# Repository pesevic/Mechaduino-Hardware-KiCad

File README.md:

# Overview
This repository contains an updated KiCad port of [jcchurch13's](https://github.com/jcchurch13/Mechaduino-Hardware) Mechaduino hardware. 

As a part of my master's thesis, I wanted to revive the Mechaduino-based [TorqueTuner](https://github.com/IDMIL/TorqueTuner), a rotary haptic device developed at the Input Devices and Music Interaction Laboratory (IDMIL) at McGill University. Since the Mechaduino has been out of production for some years, and because the original design files are in EAGLE (a now-defunct, proprietary software), I have ported the schematics and board layout to KiCad, a free and open-source (and incredibly powerful) PCB design software. 

While retaining the original circuit design, I have updated the schematics and created a new PCB layout from scratch, using KiCad's built-in component libraries. I have also included PCB fabrication/assembly files (.gbr, .drl, BOM, CPL). Most importantly, since the design is now more readily accessible, I hope it will be much easier to adapt and redesign the hardware for various stepper motors and applications.

Below, I have included some useful information if you wish to adopt or adapt the Mechaduino for your own project.

# Guide
This section serves as a guide for manufacturing and programming the Mechaduino.
## Mechaduino Summary
The [Mechaduino](https://github.com/jcchurch13/Mechaduino-Hardware) is an open-source stepper motor servo designed by [Tropical Labs](https://tropical-labs.com/mechaduino/). Its relatively small size and affordability make it attractive for mechatronics applications.

Integrated circuits on the board include a motor driver (A4954), magnetic encoder (AS5047D), 3.3 V linear voltage regulator (TLV70233), and an Arduino Zero-compatible microcontroller (ATSAMD21G18A-A). It can be powered via USB or an external 5 V source. The motor is powered through a terminal block, accepting a supply voltage between 8 V and 35 V. A range of Arduino I/O pins are accessible through the header pins, including those for I2C and SPI communication. See the schematic for more detail.

The board is designed to fit onto the back of a NEMA 17 motor.

## PCB Manufacturing
If you wish to obtain Mechaduino PCBs for yourself, you may follow what I suggest below, which is how I ordered them for myself.

For manufacturing and assembly, I used [jlcpcb.com](jlcpcb.com). Upload the zipped fabrication files to JLC, and add the PCB assembly option. Since two-layer boards can only be assembled on one side, choose the top side. The magnetic encoder and its decoupling capacitor can be soldered manually later. Upload the corresponding bill of materials and component position list .csv files. **Note that you may need to select alternative parts or reposition components in the board preview.** I have had to flip C12 and align J9 (USB connector) each time I've processed the PCBs.

## Device Assembly
Besides the Mechaduino PCB, you will need the following parts (the links direct to the parts I used):
 - [a NEMA 17 stepper motor](https://www.omc-stepperonline.com/nema-17-bipolar-45ncm-64oz-in-2a-42x42x40mm-4-wires-w-1m-cable-connector-17hs16-2004s1),
 - [a diametrically magnetized NdFeB magnet](https://www.digikey.ca/en/products/detail/radial-magnets-inc/8996/5126078),
 - an AS5074D magnetic encoder IC,
 - an 0.1 uF 0805 SMD capacitor,
 - 2.54 mm pitch header pins,
 - long M3 screws/threaded rods,
 - standoffs of some sort (I used washers), and
 - super glue.

Follow these steps (based on instructions in [Tropical Labs' manual](https://tropical-labs.com/wp-content/uploads/2018/11/Mechaduino-Manual-0.1.3.pdf)):
1. Solder the encoder and capacitor to the back of the PCB with an iron/reflow/oven. Also add the header pins.
2. Super glue the magnet onto the back of the motor shaft. Center it as much as possible.
3. Mount the PCB to the motor using the threaded rods and standoffs. The PCB should sit a couple of milimeters away from the motor.

Your Mechaduino should now be ready to be programmed.

## Programming
Flashing an Arduino Zero bootloader onto the custom MCU circuit was, for me, the most challenging part of this build. I used an ST-LINK V2 USB programmer paired with [Adafruit Adalink](https://github.com/adafruit/Adafruit_Adalink) to upload the bootloader via the PCB's SWD pins. This may be easier on Mac, but I can only speak for the Herculean procedure required for Windows users. Besides the USB programmer, you will need some way of connecting the programmer to the pins. I used an SWD breakout board connected to the programmer with jumper wires.

Follow the installation instructions on the [Adalink repository](https://github.com/adafruit/Adafruit_Adalink). Note, however, that I could not get Adalink to work with any version of Python newer than 2.7.13 (this was using Adalink 2.2.0 and OpenOCD 0.12.0). You may need to downgrade Python to an older version.

Once you have confirmed that Adalink is working in CMD, clone the [ArduinoCore-samd repository](https://github.com/arduino/arduinocore-samd) to get the bootloader. CD into `/ArduinoCore-samd/bootloaders/zero`. Wipe the board and flash the bootloader with the following two commands:
```
adalink atsamd21g18 -p stlink -w
adalink -v atsamd21g18 -p stlink -h samd21_sam_ba.hex
```
Check whether the 5888 bytes are verified. If not, unplugging and plugging the ST-LINK USB dongle into my computer seemed to fix things. Once the MCU has successfully been flashed, connect the Mechaduino to your computer via the micro-USB port. Double-pressing the reset button on the PCB should make the device appear as an Arduino Zero in Device Manager or in the Arduino IDE.

Finally, clone the [Mechaduino Firmware](https://github.com/jcchurch13/Mechaduino-Firmware) repository and upload the code to the board via the Arduino IDE. You should now have a fully functioning Mechaduino. Run the calibration routine and tests as described in [Tropical Labs' manual](https://tropical-labs.com/wp-content/uploads/2018/11/Mechaduino-Manual-0.1.3.pdf).

# License
This project is released under the [Creative Commons Attribution-ShareAlike 4.0](https://creativecommons.org/licenses/by-sa/4.0/) license, and is not endorsed by the original creator.

*No generative AI was used in any part of this project.*

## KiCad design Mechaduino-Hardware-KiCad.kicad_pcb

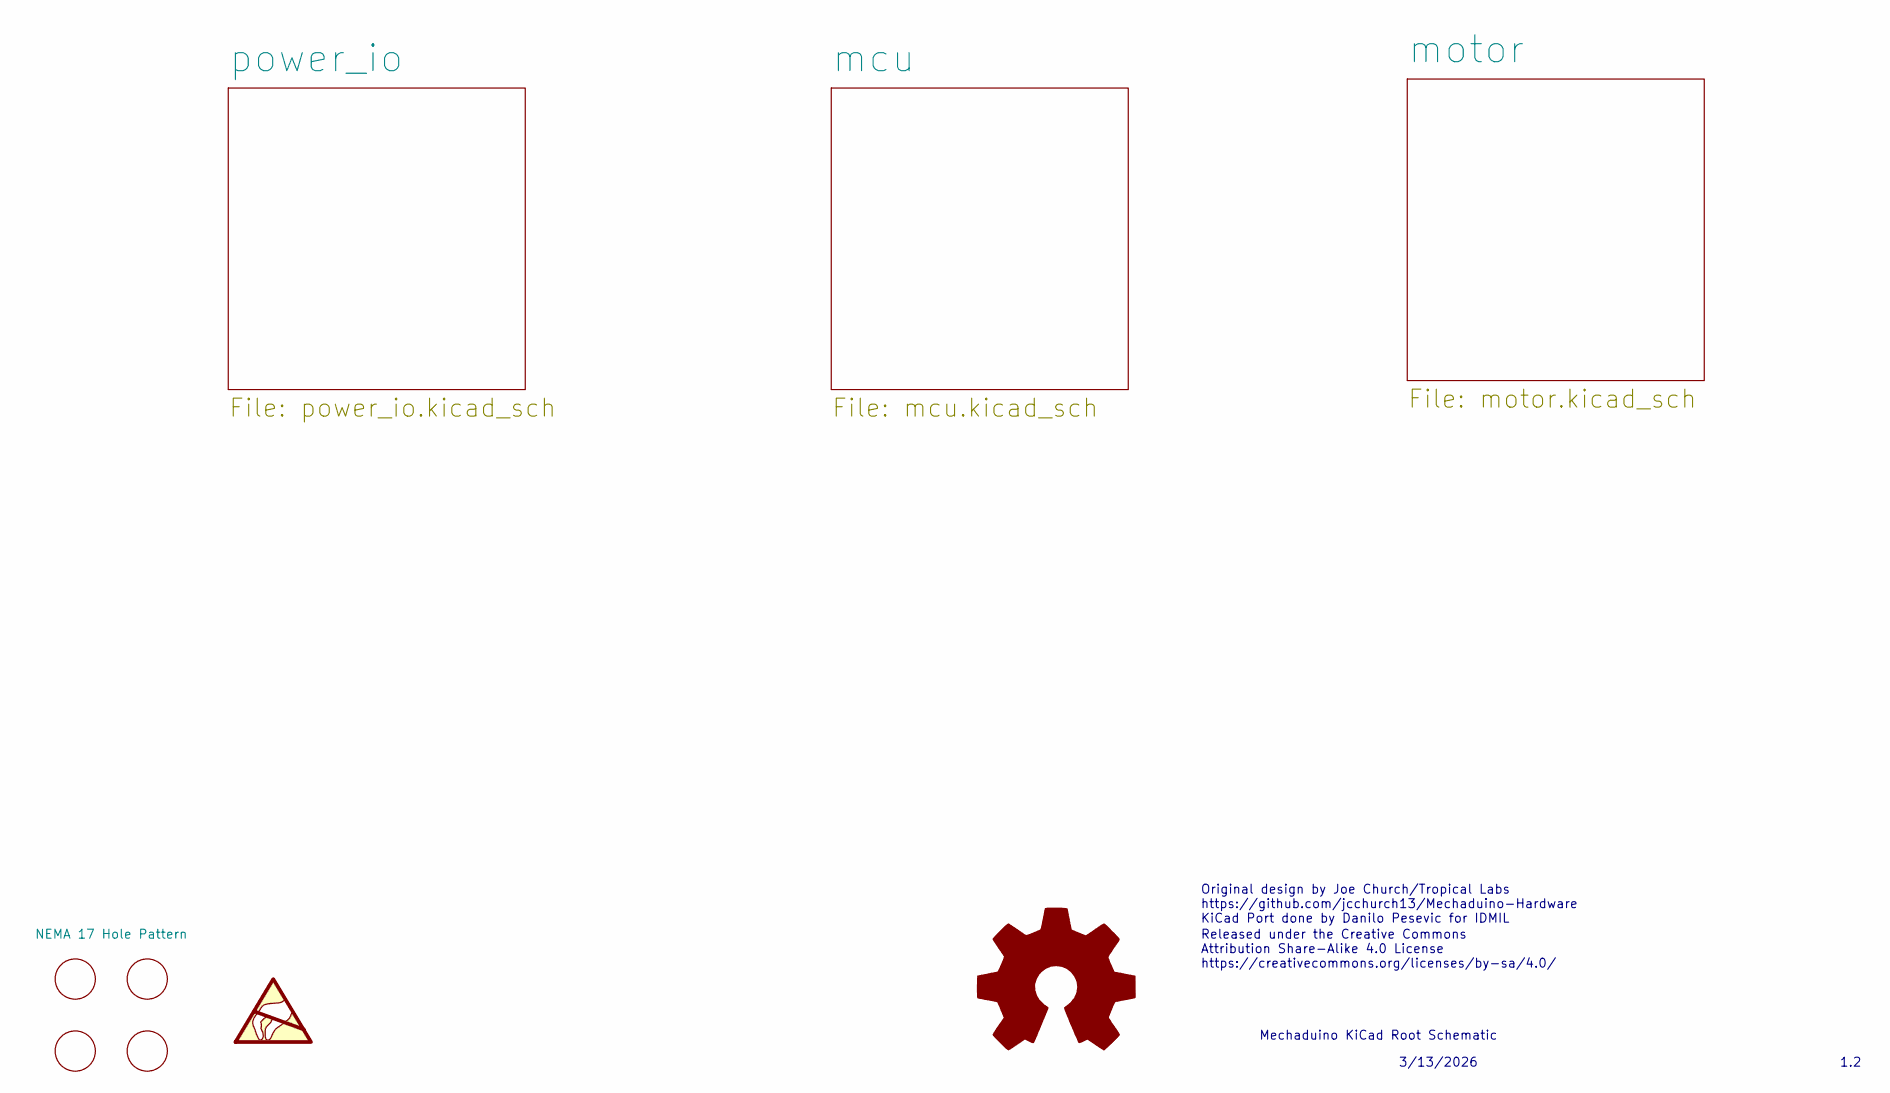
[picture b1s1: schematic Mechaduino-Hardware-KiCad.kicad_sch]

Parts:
J13: NEMA 17 Hole Pattern

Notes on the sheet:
Mechaduino KiCad Root Schematic
Original design by Joe Church/Tropical Labs https://github.com/jcchurch13/Mechaduino-Hardware KiCad Port done by Danilo Pesevic for IDMIL
3/13/2026
Released under the Creative Commons Attribution Share-Alike 4.0 License https://creativecommons.org/licenses/by-sa/4.0/
1.2

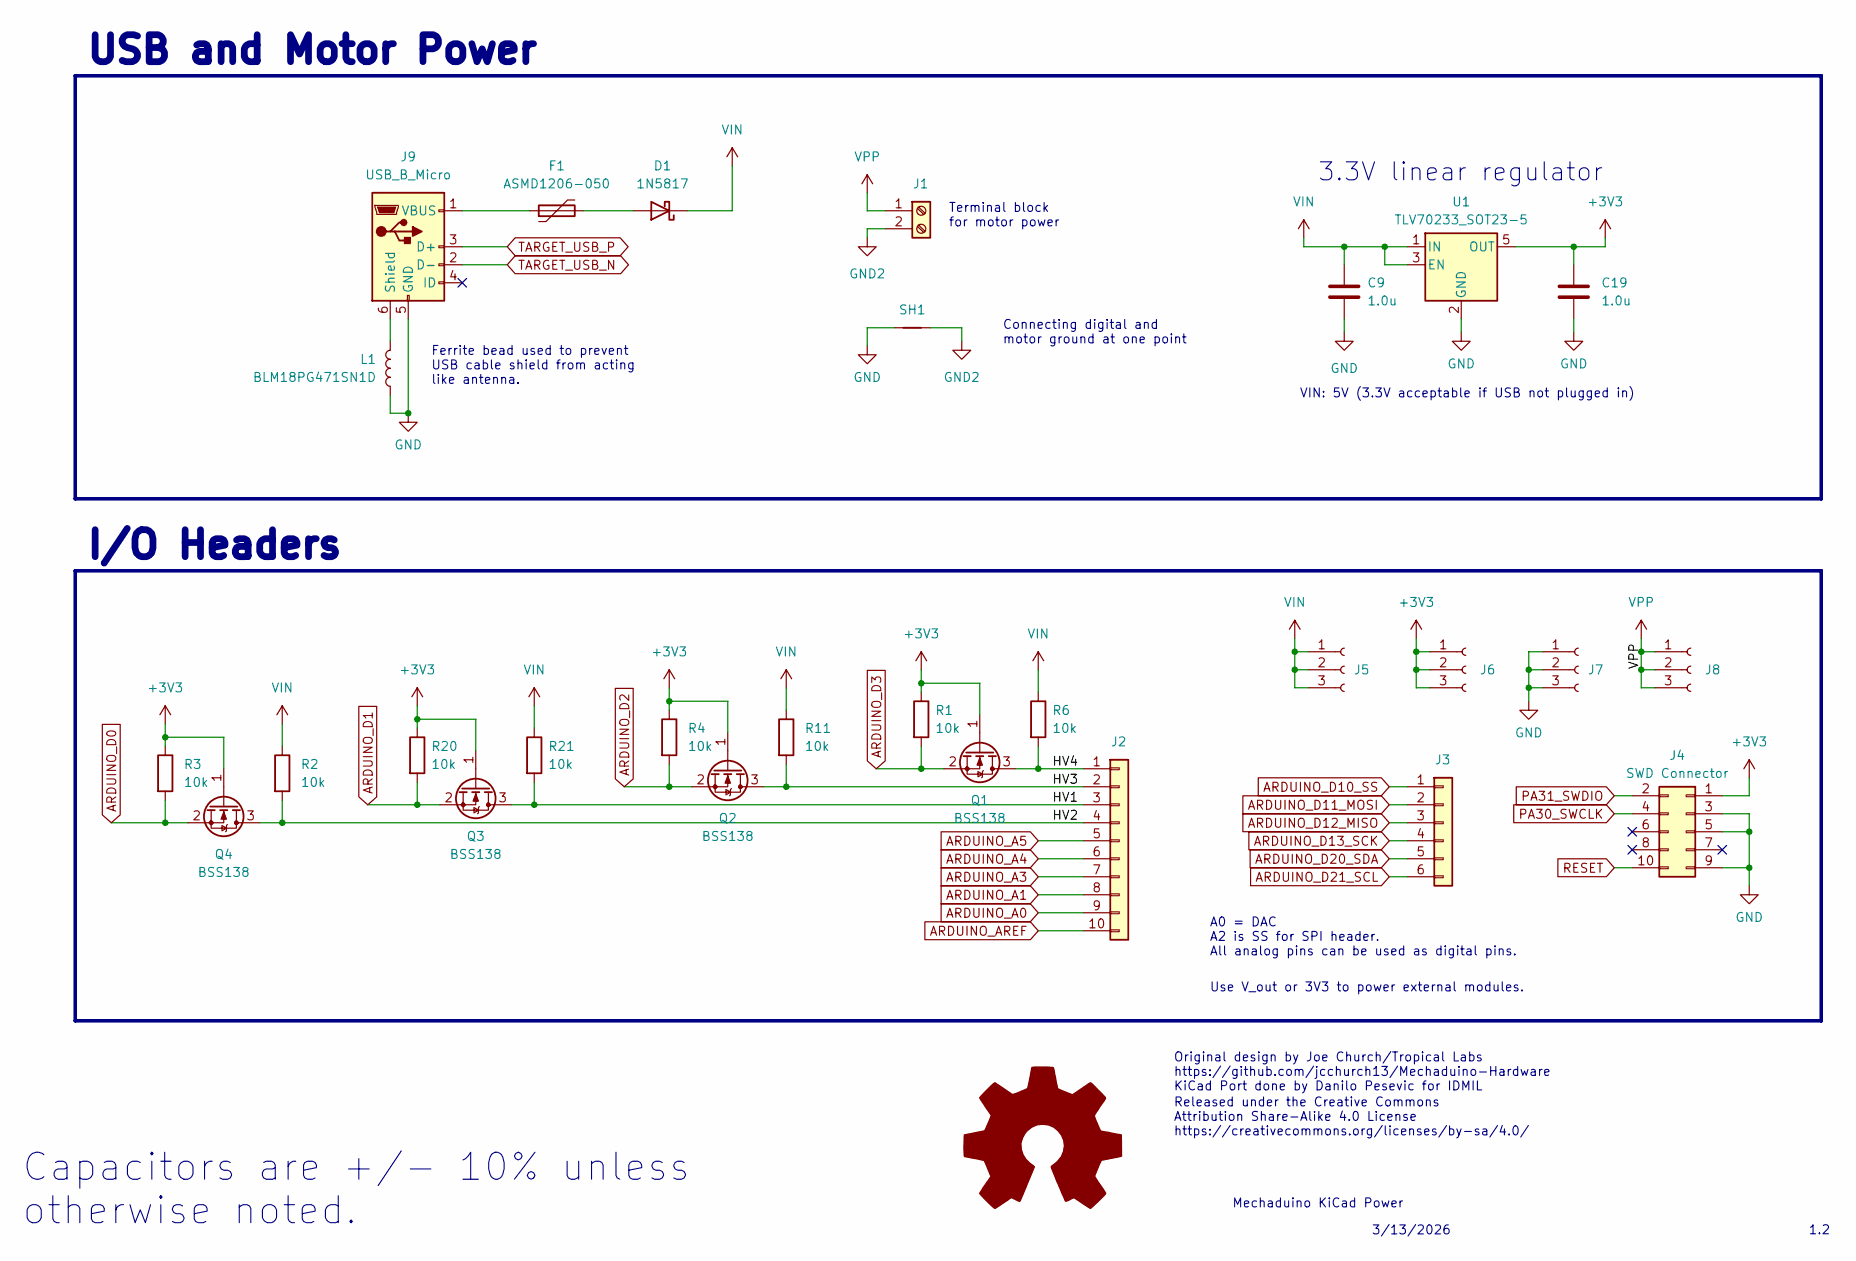
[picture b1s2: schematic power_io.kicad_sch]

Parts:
C9, C19: 1.0u; C_0402_1005Metric
D1: 1N5817; D_SOD-123F
F1: ASMD1206-050; Fuse_1206_3216Metric
J1: Screw_Terminal_01x02; TerminalBlock_Phoenix_MKDS-1,5-2_1x02_P5.00mm_Horizontal
J2: Conn_01x10; PinHeader_1x10_P2.54mm_Vertical
J3: Conn_01x06; PinHeader_2x03_P2.54mm_Vertical
J4: SWD Connector; PinSocket_2x05_P1.27mm_Vertical
J5, J6, J7, J8: Conn_01x03_Socket; PinHeader_1x03_P2.54mm_Vertical
J9: USB_B_Micro; USB_Micro-AB_Molex_47590-0001
L1: BLM18PG471SN1D; L_0603_1608Metric
Q1, Q2, Q3, Q4: BSS138; SOT-23-3
R1, R2, R3, R4, R6, R11, R20, R21: 10k; R_0402_1005Metric
SH1: NetTie_2; NetTie-2_THT_Pad1.0mm
U1: TLV70233_SOT23-5; SOT-23-5

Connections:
+3V3: C19.1, J4.1, J6.1, J6.2, J6.3, Q1.1 (G), Q2.1 (G), Q3.1 (G), Q4.1 (G), R1.1, R3.1, R4.1, R20.1, U1.5 (OUT); also elsewhere on the board
/power_io/HV1: J2.3, Q3.3 (D), R21.2
/power_io/HV2: J2.4, Q4.3 (D), R2.2
/power_io/HV3: J2.2, Q2.3 (D), R11.2
/power_io/HV4: J2.1, Q1.3 (D), R6.2
ARDUINO_A0: J2.9; also elsewhere on the board
ARDUINO_A1: J2.8; also elsewhere on the board
ARDUINO_A3: J2.7; also elsewhere on the board
ARDUINO_A4: J2.6; also elsewhere on the board
ARDUINO_A5: J2.5; also elsewhere on the board
ARDUINO_AREF: J2.10; also elsewhere on the board
ARDUINO_D0: Q4.2 (S), R3.2; also elsewhere on the board
ARDUINO_D1: Q3.2 (S), R20.2; also elsewhere on the board
ARDUINO_D2: Q2.2 (S), R4.2; also elsewhere on the board
ARDUINO_D3: Q1.2 (S), R1.2; also elsewhere on the board
ARDUINO_D10_SS: J3.1; also elsewhere on the board
ARDUINO_D11_MOSI: J3.2; also elsewhere on the board
ARDUINO_D12_MISO: J3.3; also elsewhere on the board
ARDUINO_D13_SCK: J3.4; also elsewhere on the board
ARDUINO_D20_SDA: J3.5; also elsewhere on the board
ARDUINO_D21_SCL: J3.6; also elsewhere on the board
GND: C9.2, C19.2, J4.3, J4.5, J4.9, J7.1, J7.2, J7.3, J9.5 (GND), L1.1, SH1.1, U1.2 (GND); also elsewhere on the board
GND2: J1.2, SH1.2; also elsewhere on the board
unnamed: D1.2 (A), F1.2
unnamed: J9.6 (Shield), L1.2
unnamed: F1.1, J9.1 (VBUS)
PA30_SWCLK: J4.4; also elsewhere on the board
PA31_SWDIO: J4.2; also elsewhere on the board
RESET: J4.10; also elsewhere on the board
TARGET_USB_N: J9.2 (D-); also elsewhere on the board
TARGET_USB_P: J9.3 (D+); also elsewhere on the board
VIN: C9.1, D1.1 (K), J5.1, J5.2, J5.3, R2.1, R6.1, R11.1, R21.1, U1.1 (IN), U1.3 (EN)
VPP: J1.1, J8.1, J8.2, J8.3; also elsewhere on the board

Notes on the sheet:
1.2
3.3V linear regulator
Use V_out or 3V3 to power external modules.
Mechaduino KiCad Power
Ferrite bead used to prevent USB cable shield from acting like antenna.
VIN: 5V (3.3V acceptable if USB not plugged in)
3/13/2026
Original design by Joe Church/Tropical Labs https://github.com/jcchurch13/Mechaduino-Hardware KiCad Port done by Danilo Pesevic for IDMIL
Connecting digital and motor ground at one point
Capacitors are +/- 10% unless otherwise noted.
Terminal block for motor power
I/O Headers
Released under the Creative Commons Attribution Share-Alike 4.0 License https://creativecommons.org/licenses/by-sa/4.0/
USB and Motor Power
A0 = DAC A2 is SS for SPI header. All analog pins can be used as digital pins.

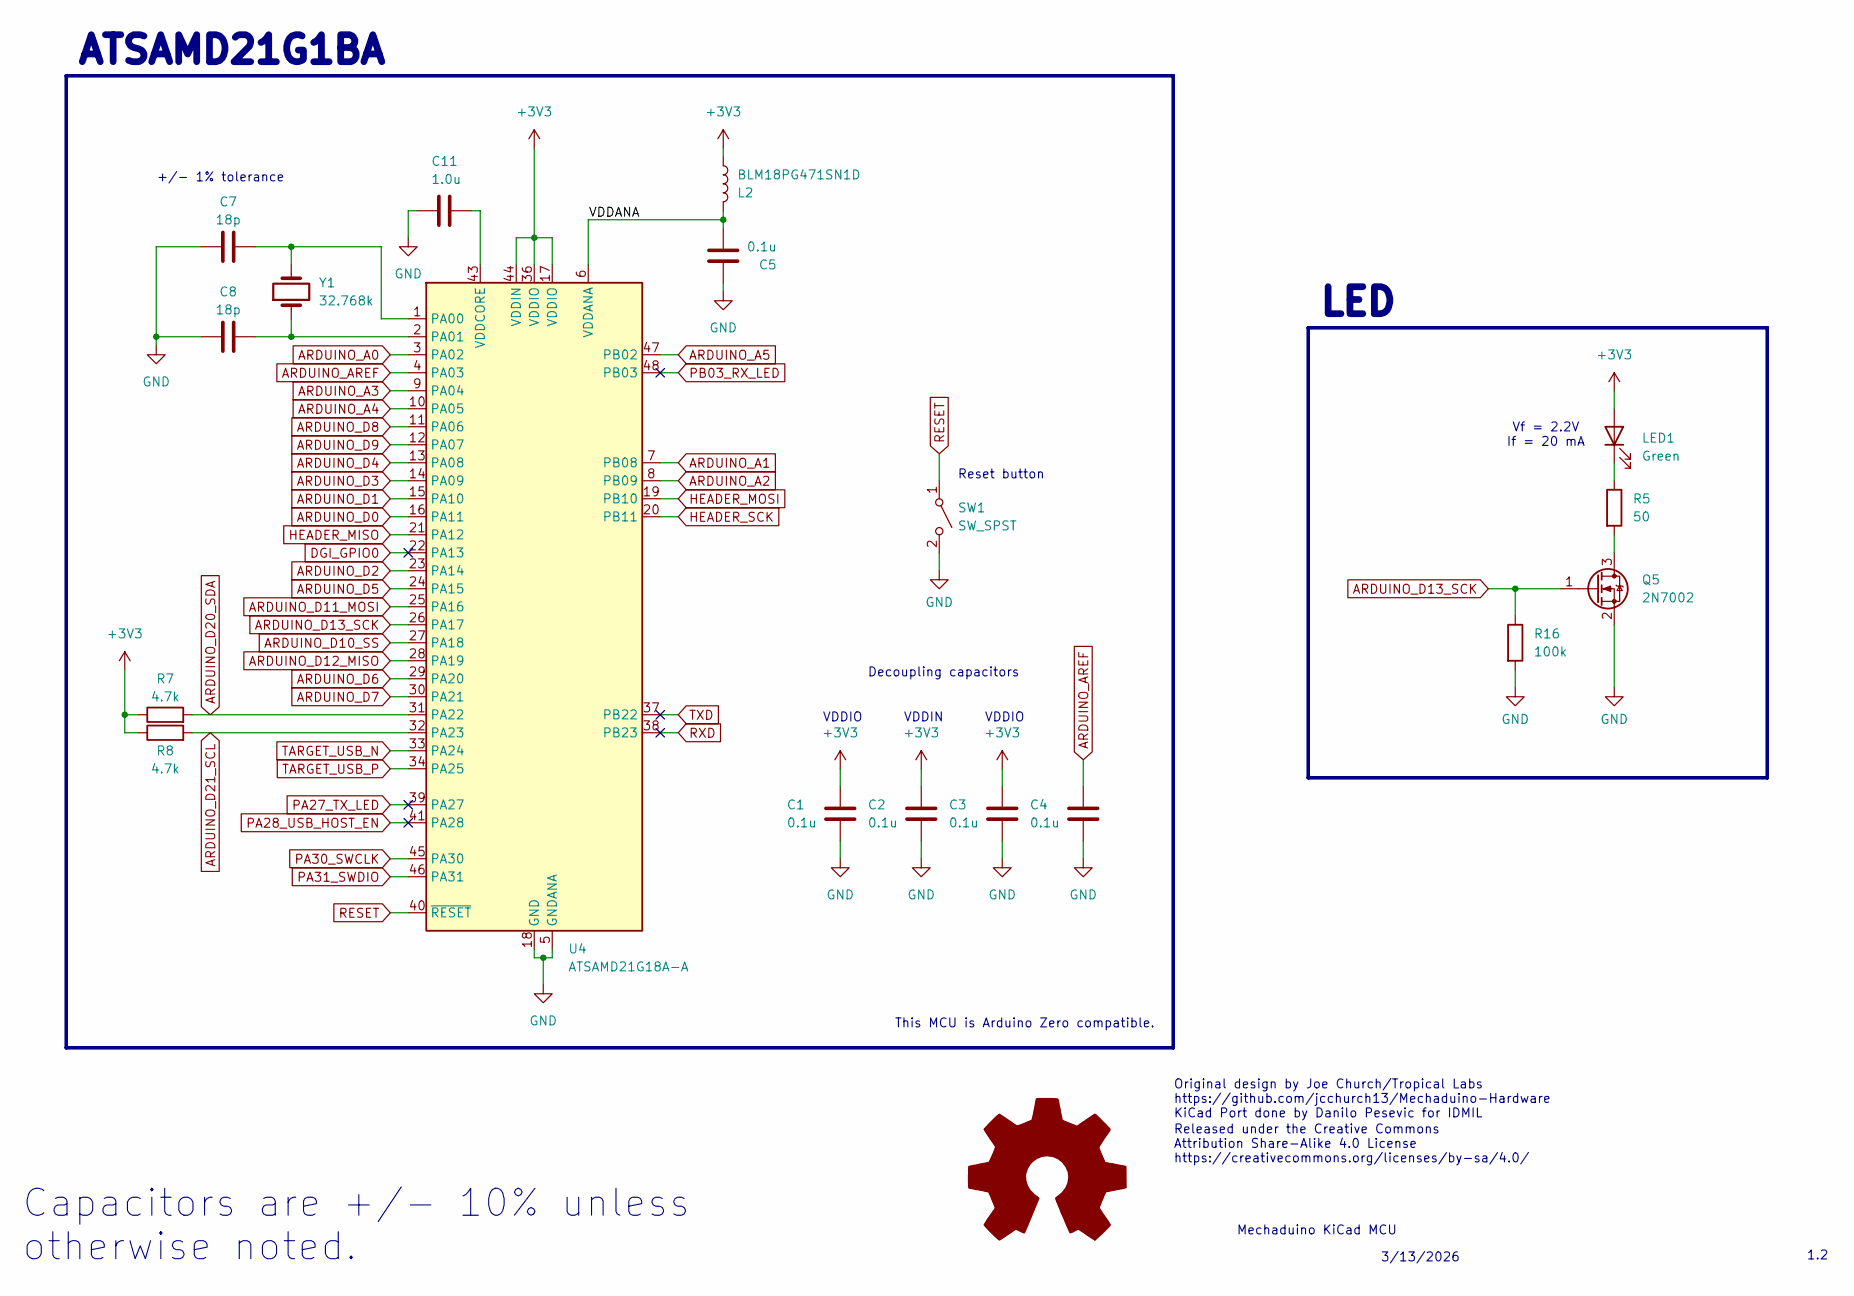
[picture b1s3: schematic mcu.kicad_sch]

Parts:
C1, C2, C3, C4, C5: 0.1u; C_0402_1005Metric
C7, C8: 18p; C_0603_1608Metric
C11: 1.0u; C_0402_1005Metric
L2: BLM18PG471SN1D; L_0603_1608Metric
LED1: Green; LED_0805_2012Metric
Q5: 2N7002; SOT-323_SC-70
R5: 50; R_0402_1005Metric
R7, R8: 4.7k; R_0402_1005Metric
R16: 100k; R_0402_1005Metric
SW1: SW_SPST; SW_SPST_PTS810
U4: ATSAMD21G18A-A; TQFP-48_7x7mm_P0.5mm
Y1: 32.768k; Crystal_SMD_2012-2Pin_2.0x1.2mm

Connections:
+3V3: C1.1, C2.1, C3.1, L2.1, LED1.2 (A), R7.1, R8.1, U4.17 (VDDIO), U4.36 (VDDIO), U4.44 (VDDIN); also elsewhere on the board
/mcu/VDDANA: C5.2, L2.2, U4.6 (VDDANA)
ARDUINO_A0: U4.3 (PA02); also elsewhere on the board
ARDUINO_A1: U4.7 (PB08); also elsewhere on the board
ARDUINO_A2: U4.8 (PB09); also elsewhere on the board
ARDUINO_A3: U4.9 (PA04); also elsewhere on the board
ARDUINO_A4: U4.10 (PA05); also elsewhere on the board
ARDUINO_A5: U4.47 (PB02); also elsewhere on the board
ARDUINO_AREF: C4.1, U4.4 (PA03); also elsewhere on the board
ARDUINO_D0: U4.16 (PA11); also elsewhere on the board
ARDUINO_D1: U4.15 (PA10); also elsewhere on the board
ARDUINO_D2: U4.23 (PA14); also elsewhere on the board
ARDUINO_D3: U4.14 (PA09); also elsewhere on the board
ARDUINO_D4: U4.13 (PA08); also elsewhere on the board
ARDUINO_D5: U4.24 (PA15); also elsewhere on the board
ARDUINO_D6: U4.29 (PA20); also elsewhere on the board
ARDUINO_D7: U4.30 (PA21); also elsewhere on the board
ARDUINO_D8: U4.11 (PA06); also elsewhere on the board
ARDUINO_D9: U4.12 (PA07); also elsewhere on the board
ARDUINO_D10_SS: U4.27 (PA18); also elsewhere on the board
ARDUINO_D11_MOSI: U4.25 (PA16); also elsewhere on the board
ARDUINO_D12_MISO: U4.28 (PA19); also elsewhere on the board
ARDUINO_D13_SCK: Q5.1 (G), R16.1, U4.26 (PA17); also elsewhere on the board
ARDUINO_D20_SDA: R7.2, U4.31 (PA22); also elsewhere on the board
ARDUINO_D21_SCL: R8.2, U4.32 (PA23); also elsewhere on the board
DGI_GPIO0: U4.22 (PA13)
GND: C1.2, C2.2, C3.2, C4.2, C5.1, C7.1, C8.1, C11.2, Q5.2 (S), R16.2, SW1.2 (B), U4.5 (GNDANA), U4.18 (GND), U4.35 (GND), U4.42 (GND); also elsewhere on the board
HEADER_MISO: U4.21 (PA12); also elsewhere on the board
HEADER_MOSI: U4.19 (PB10); also elsewhere on the board
HEADER_SCK: U4.20 (PB11); also elsewhere on the board
unnamed: LED1.1 (K), R5.1
unnamed: Q5.3 (D), R5.2
unnamed: C7.2, U4.1 (PA00), Y1.2
unnamed: C8.2, U4.2 (PA01), Y1.1
unnamed: C11.1, U4.43 (VDDCORE)
PA27_TX_LED: U4.39 (PA27)
PA28_USB_HOST_EN: U4.41 (PA28)
PA30_SWCLK: U4.45 (PA30); also elsewhere on the board
PA31_SWDIO: U4.46 (PA31); also elsewhere on the board
PB03_RX_LED: U4.48 (PB03)
RESET: SW1.1 (A), U4.40 (~RESET); also elsewhere on the board
RXD: U4.38 (PB23)
TARGET_USB_N: U4.33 (PA24); also elsewhere on the board
TARGET_USB_P: U4.34 (PA25); also elsewhere on the board
TXD: U4.37 (PB22)

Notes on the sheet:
VDDIO
Reset button
Capacitors are +/- 10% unless otherwise noted.
LED
VDDIN
Released under the Creative Commons Attribution Share-Alike 4.0 License https://creativecommons.org/licenses/by-sa/4.0/
Original design by Joe Church/Tropical Labs https://github.com/jcchurch13/Mechaduino-Hardware KiCad Port done by Danilo Pesevic for IDMIL
ATSAMD21G1BA
+/- 1% tolerance
Vf = 2.2V If = 20 mA
Decoupling capacitors
Mechaduino KiCad MCU
This MCU is Arduino Zero compatible.
1.2
3/13/2026

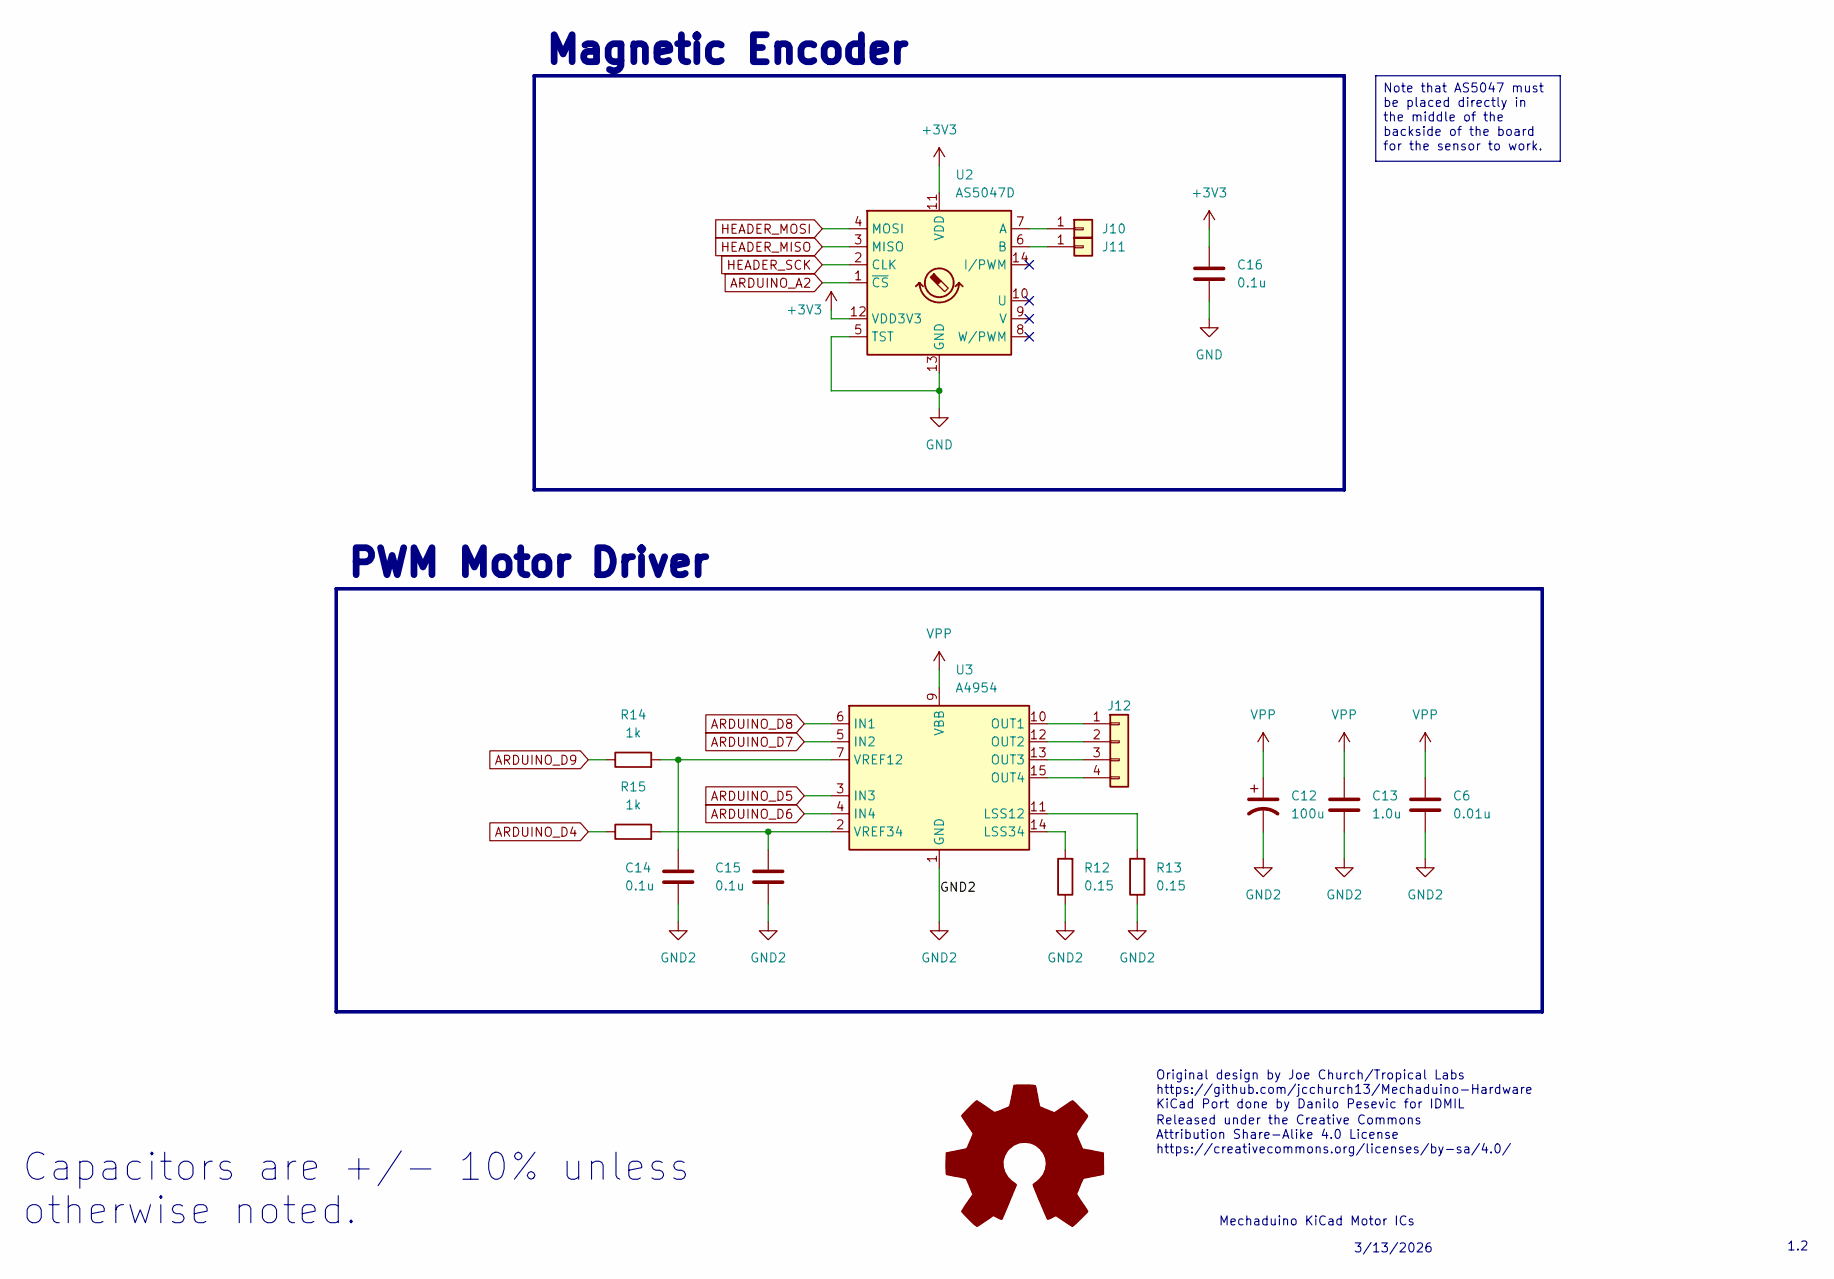
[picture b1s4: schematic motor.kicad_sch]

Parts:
C6: 0.01u; C_0603_1608Metric
C12: 100u; CP_Elec_6.3x7.7
C13: 1.0u; C_0603_1608Metric
C14, C15: 0.1u; C_0402_1005Metric
C16: 0.1u; C_0805_2012Metric_Pad1.18x1.45mm_HandSolder
J10, J11: Conn_01x01; PinHeader_1x01_P2.54mm_Vertical
J12: Conn_01x04; PinHeader_1x04_P2.54mm_Vertical
R12, R13: 0.15; R_1206_3216Metric
R14, R15: 1k; R_0402_1005Metric
U2: AS5047D; TSSOP-14_4.4x5mm_P0.65mm
U3: A4954; TSSOP-16-1EP_4.4x5mm_P0.65mm_EP3x3mm_ThermalVias

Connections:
+3V3: C16.1, U2.11 (VDD), U2.12 (VDD3V3); also elsewhere on the board
ARDUINO_A2: U2.1 (~CS); also elsewhere on the board
ARDUINO_D4: R15.1; also elsewhere on the board
ARDUINO_D5: U3.3 (IN3); also elsewhere on the board
ARDUINO_D6: U3.4 (IN4); also elsewhere on the board
ARDUINO_D7: U3.5 (IN2); also elsewhere on the board
ARDUINO_D8: U3.6 (IN1); also elsewhere on the board
ARDUINO_D9: R14.1; also elsewhere on the board
GND: C16.2, U2.5 (TST), U2.13 (GND); also elsewhere on the board
GND2: C6.2, C12.2, C13.2, C14.2, C15.2, R12.1, R13.1, U3.1 (GND), U3.8 (GND), U3.17 (GND); also elsewhere on the board
HEADER_MISO: U2.3 (MISO); also elsewhere on the board
HEADER_MOSI: U2.4 (MOSI); also elsewhere on the board
HEADER_SCK: U2.2 (CLK); also elsewhere on the board
unnamed: J10.1, U2.7 (A)
unnamed: J11.1, U2.6 (B)
unnamed: J12.1, U3.10 (OUT1)
unnamed: J12.2, U3.12 (OUT2)
unnamed: J12.3, U3.13 (OUT3)
unnamed: J12.4, U3.15 (OUT4)
unnamed: R13.2, U3.11 (LSS12)
unnamed: R12.2, U3.14 (LSS34)
unnamed: C14.1, R14.2, U3.7 (VREF12)
unnamed: C15.1, R15.2, U3.2 (VREF34)
VPP: C6.1, C12.1, C13.1, U3.9 (VBB), U3.16 (VBB); also elsewhere on the board

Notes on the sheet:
3/13/2026
Original design by Joe Church/Tropical Labs https://github.com/jcchurch13/Mechaduino-Hardware KiCad Port done by Danilo Pesevic for IDMIL
Released under the Creative Commons Attribution Share-Alike 4.0 License https://creativecommons.org/licenses/by-sa/4.0/
1.2
Mechaduino KiCad Motor ICs
Magnetic Encoder
Capacitors are +/- 10% unless otherwise noted.
PWM Motor Driver
Note that AS5047 must be placed directly in the middle of the backside of the board for the sensor to work.

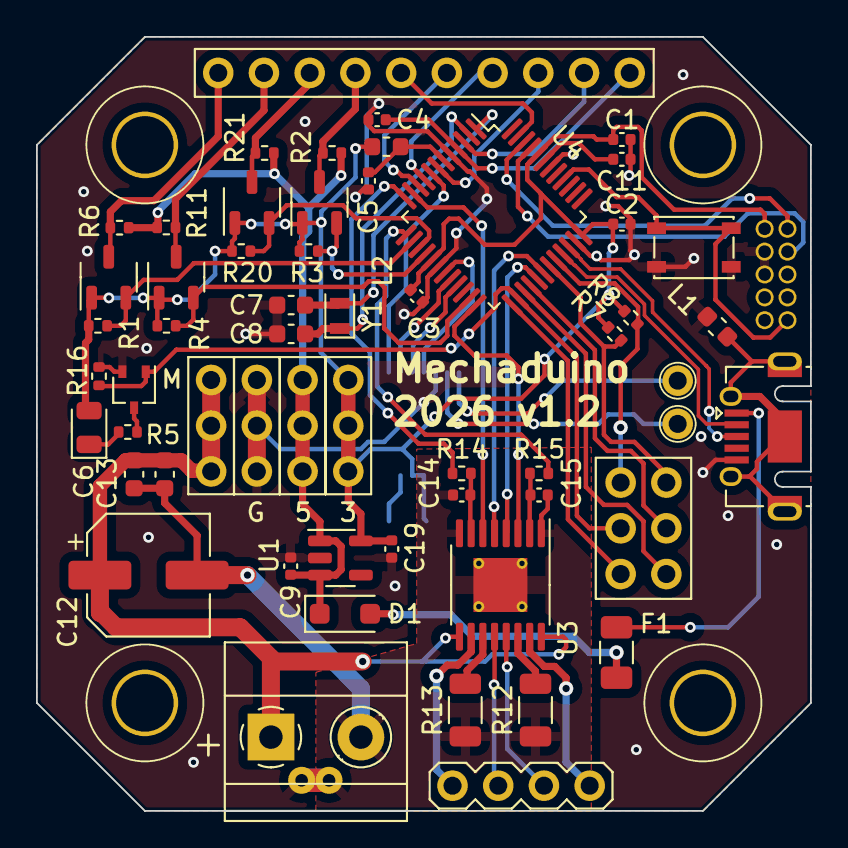
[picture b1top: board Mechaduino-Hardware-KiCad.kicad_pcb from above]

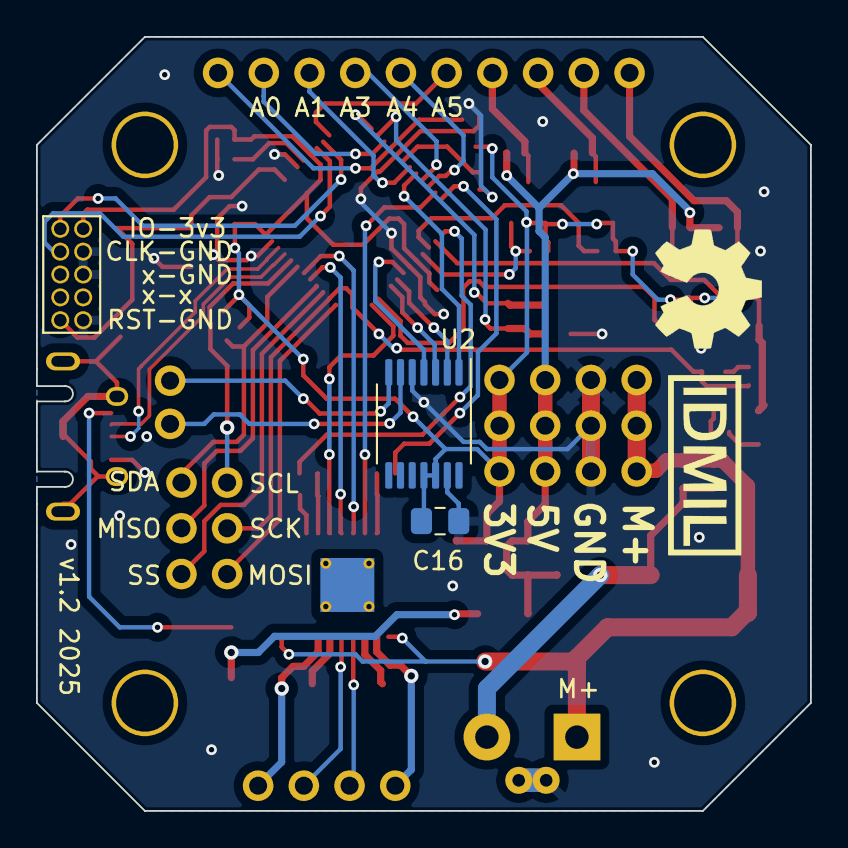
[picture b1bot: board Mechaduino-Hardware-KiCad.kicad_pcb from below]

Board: 2 copper layers, 43.0 x 43.0 mm, 62 parts (3 on the bottom side), 59 nets.

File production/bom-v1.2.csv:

Designator,Footprint,Quantity,Value,LCSC Part #
"C1, C14, C15, C16, C2, C3, C4, C5",402,8,0.1u,C169842
"C11, C19, C9",402,3,1.0u,C29266
C12,CP_Elec_6.3x7.7,1,100u,C178560
C13,603,1,1.0u,C5673
C6,603,1,0.01u,C1589
"C7, C8",603,2,18p,C165734
D1,D_SOD-123F,1,SMF5.0CA,C283867
F1,1206,1,ASMD1206-050,C883127
J1,"TerminalBlock_Phoenix_MKDS-1,5-2_1x02_P5.00mm_Horizontal",1,Screw_Terminal_01x02,C3817933
J9,USB_Micro-AB_Molex_47590-0001,1,USB_B_Micro,C136001
"L1, L2",603,2,BLM18PG471SN1D,C97853
LED1,805,1,Green,C2899888
"Q1, Q2, Q3, Q4",SOT-23-3,4,BSS138,C534601
Q5,SOT-323_SC-70,1,2N7002,C139444
"R1, R11, R2, R20, R21, R3, R4, R6",402,8,10k,C71617
"R12, R13",1206,2,0.15,C37936
"R14, R15",402,2,1k,C71623
R16,402,1,100k,C481918
R5,402,1,330,C25104
"R7, R8",402,2,4.7k,C482193
SW1,SW_SPST_PTS810,1,SW_SPST,C221896
U1,SOT-23-5,1,TLV70233_SOT23-5,C110287
U2,TSSOP-14_4.4x5mm_P0.65mm,1,AS5047D,C2693743
U3,TSSOP-16-1EP_4.4x5mm_P0.65mm_EP3x3mm_ThermalVias,1,A4954,C2688265
U4,TQFP-48_7x7mm_P0.5mm,1,ATSAMD21G18A-A,C78624
Y1,Crystal_SMD_2012-2Pin_2.0x1.2mm,1,32.768k,C907552

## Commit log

2026-03-13 Initial commit, hardware v1.2.
2026-03-13 Updated README.md with overview
2026-03-14 Updated README.md, added image, and removed unnecessary schematic files
2026-03-14 Fixed image path in README.md
